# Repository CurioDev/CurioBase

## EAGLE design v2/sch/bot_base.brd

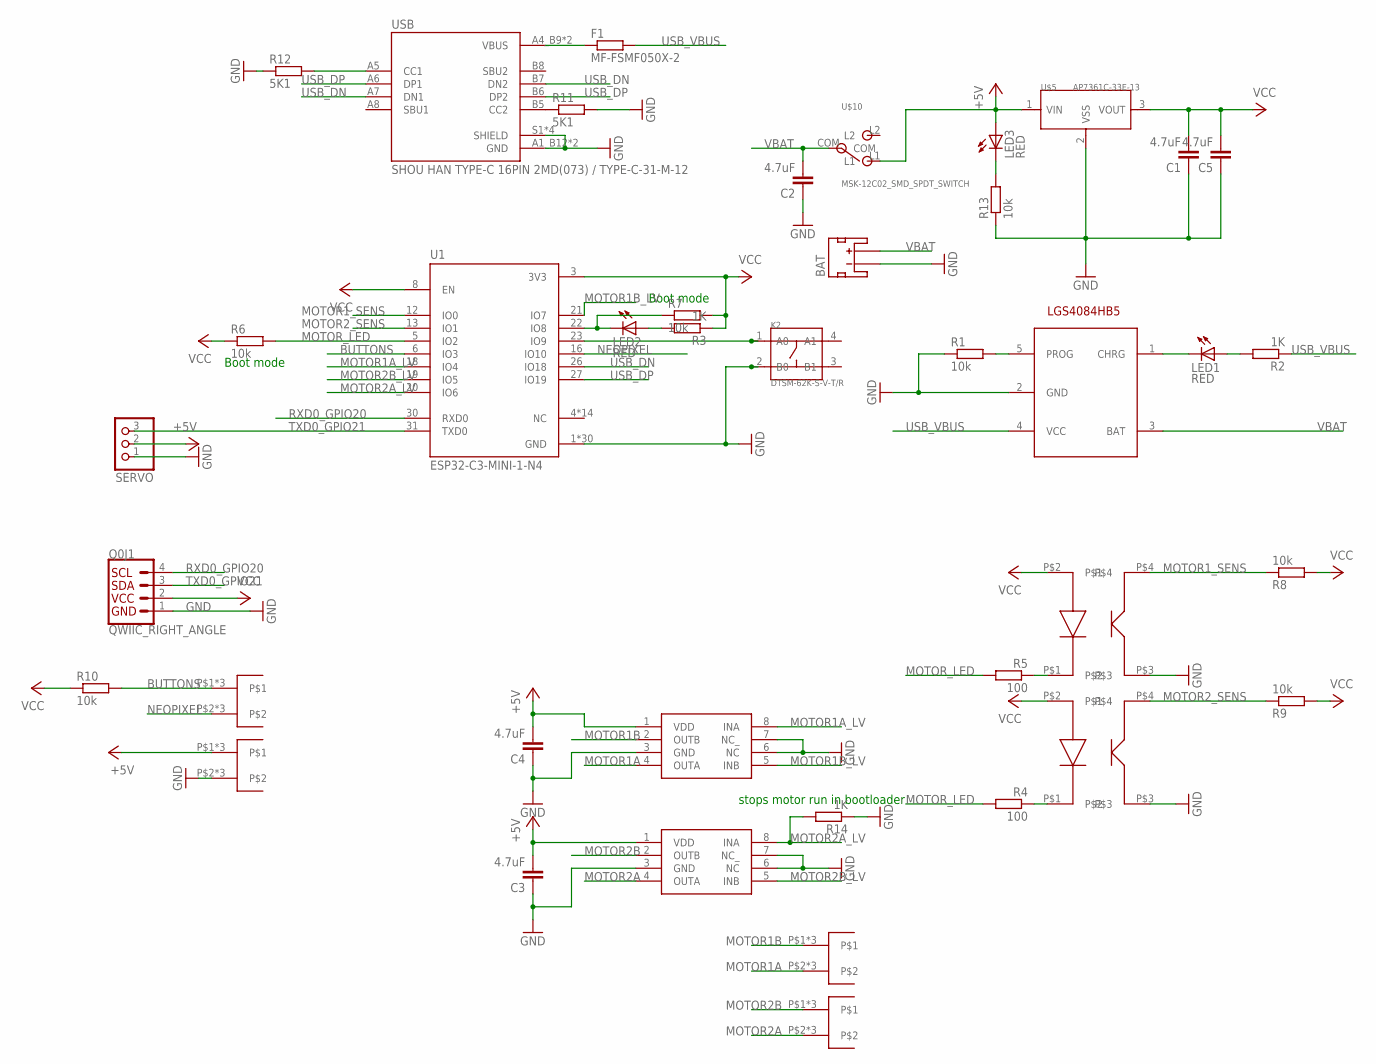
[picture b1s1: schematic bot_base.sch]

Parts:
BAT: C47647 / S2B-PH-SM4-TB; JST-2-SMD
C1, C2, C3, C4, C5: 4.7uF; C0805
F1: MF-FSMF050X-2; R0603
K2: DTSM-62K-S-V-T/R; SW4-SMD-6.0X6.0X5.0MM
LED1, LED2, LED3: RED; CHIPLED_0603
Q0: QWIIC_RIGHT_ANGLE; JST04_1MM_RA
R1, R6, R7, R8, R9, R10, R13: 10k; R0603
R2, R3, R14: 1K; R0603
R4, R5: 100; R0603
R11, R12: 5K1; R0603
SERVO: PINHD-1X03_2.54-S; 1X03-S
U1: ESP32-C3-MINI-1-N4; XCVR_ESP32-C3-MINI-1-N4
U4: LGS4084HB5; SOT23-5
U$1, U$2: XL-ITR9707
U$3, U$4: GR6205; SOP8
U$5: AP7361C-33E-13; SOT223
U$6, U$7, U$8, U$9: PCBSIDE2
U$10: MSK-12C02_SMD_SPDT_SWITCH; MSK-12C02
USB: SHOU HAN TYPE-C 16PIN 2MD(073) / TYPE-C-31-M-12; HRO_TYPE-C-31-M-12

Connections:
+5V: C3.2, C4.2, LED3.A, SERVO.2, U$3.1 (VDD), U$4.1 (VDD), U$5.1 (VIN), U$9.P$1, U$9.P$3, U$9.P$4, U$10.L1
BOOT: K2.1 (A0), U1.23 (IO9)
BUTTONS: R10.2, U1.6 (IO3), U$8.P$1, U$8.P$3, U$8.P$4
GND: BAT.1 (-), C1.1, C2.1, C3.1, C4.1, C5.1, K2.2 (B0), Q0.1, R1.1, R11.2, R12.1, R13.1, R14.1, SERVO.1, U1.1 (GND), U1.2 (GND), U1.11 (GND), U1.14 (GND), U1.36 (GND), U1.37 (GND), U1.38 (GND), U1.39 (GND), U1.40 (GND), U1.41 (GND), U1.42 (GND), U1.43 (GND), U1.44 (GND), U1.45 (GND), U1.46 (GND), U1.47 (GND), U1.48 (GND), U1.49_1 (GND), U1.49_2 (GND), U1.49_3 (GND), U1.49_4 (GND), U1.49_5 (GND), U1.49_6 (GND), U1.49_7 (GND), U1.49_8 (GND), U1.49_9 (GND), U1.50 (GND), U1.51 (GND), U1.52 (GND), U1.53 (GND), U4.2 (GND), U$1.P$3, U$2.P$3, U$3.3 (GND), U$3.6 (NC), U$3.7 (NC_), U$4.3 (GND), U$4.6 (NC), U$4.7 (NC_), U$5.2 (VSS), U$9.P$2, U$9.P$5, U$9.P$6, USB.A1_B12 (GND), USB.B1_A12 (GND), USB.S1 (SHIELD), USB.S2 (SHIELD), USB.S3 (SHIELD), USB.S4 (SHIELD)
MOTOR1A: U$3.4 (OUTA), U$6.P$2, U$6.P$5, U$6.P$6
MOTOR1A_LV: U1.18 (IO4), U$3.8 (INA)
MOTOR1B: U$3.2 (OUTB), U$6.P$1, U$6.P$3, U$6.P$4
MOTOR1B_LV: U1.21 (IO7), U$3.5 (INB)
MOTOR1_SENS: R8.1, U1.12 (IO0), U$1.P$4
MOTOR2A: U$4.4 (OUTA), U$7.P$2, U$7.P$5, U$7.P$6
MOTOR2A_LV: R14.2, U1.20 (IO6), U$4.8 (INA)
MOTOR2B: U$4.2 (OUTB), U$7.P$1, U$7.P$3, U$7.P$4
MOTOR2B_LV: U1.19 (IO5), U$4.5 (INB)
MOTOR2_SENS: R9.1, U1.13 (IO1), U$2.P$4
MOTOR_LED: R4.2, R5.2, R6.2, U1.5 (IO2)
unnamed: LED1.C, U4.1 (CHRG)
unnamed: LED3.C, R13.2
unnamed: R5.1, U$1.P$1
unnamed: LED1.A, R2.2
unnamed: R4.1, U$2.P$1
unnamed: LED2.A, R3.2
unnamed: R11.1, USB.B5 (CC2)
unnamed: LED2.C, R7.1, U1.22 (IO8)
unnamed: R12.2, USB.A5 (CC1)
unnamed: R1.2, U4.5 (PROG)
NEOPIXEL: U1.16 (IO10), U$8.P$2, U$8.P$5, U$8.P$6
RXD0_GPIO20: Q0.4, U1.30 (RXD0)
TXD0_GPIO21: Q0.3, SERVO.3, U1.31 (TXD0)
USB_DN: U1.26 (IO18), USB.A7 (DN1), USB.B7 (DN2)
USB_DP: U1.27 (IO19), USB.A6 (DP1), USB.B6 (DP2)
USB_VBUS: F1.2, R2.1, U4.4 (VCC)
VBAT: BAT.2 (+), C2.2, U4.3 (BAT), U$10.COM
VBUS1: F1.1, USB.A4_B9 (VBUS), USB.B4_A9 (VBUS)
VCC: C1.2, C5.2, Q0.2, R3.1, R6.1, R7.2, R8.2, R9.2, R10.1, U1.3 (3V3), U1.8 (EN), U$1.P$2, U$2.P$2, U$5.3 (VOUT)

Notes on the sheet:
LGS4084HB5
Boot mode
stops motor run in bootloader

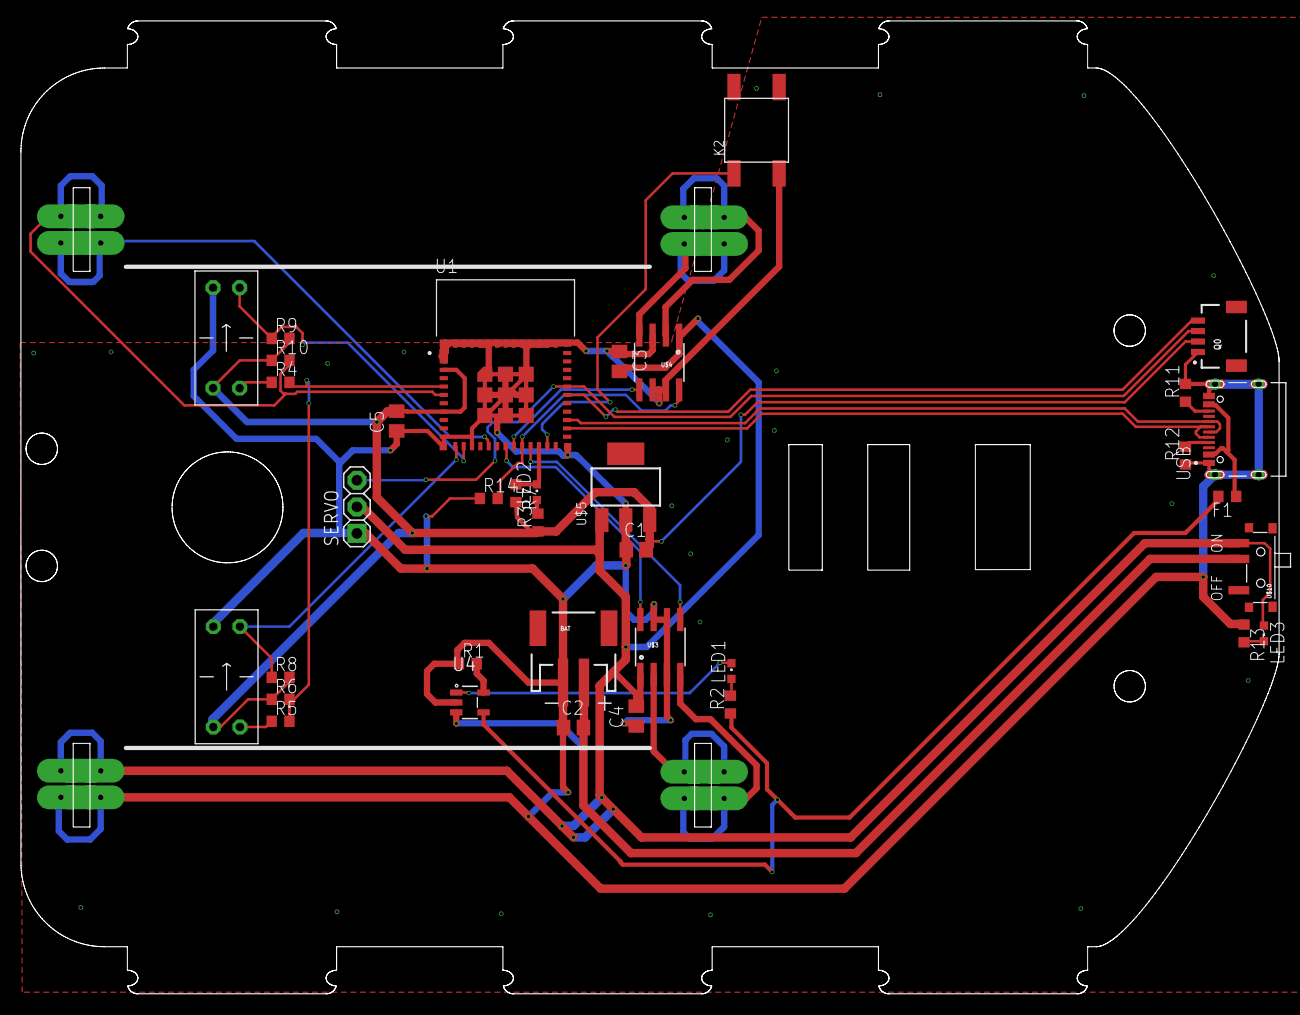
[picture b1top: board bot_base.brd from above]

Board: 2 copper layers, 120.3 x 93.0 mm, 40 parts (0 on the bottom side), 34 nets.

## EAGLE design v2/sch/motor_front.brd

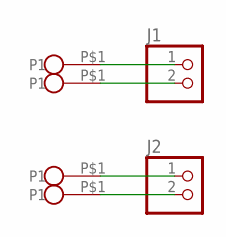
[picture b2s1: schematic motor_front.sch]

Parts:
J1, J2: PINHD-1X2; 1X02
U$1, U$2, U$3, U$4: BIGHOLE

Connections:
unnamed: J1.1, U$1.P$1
unnamed: J1.2, U$2.P$1
unnamed: J2.1, U$4.P$1
unnamed: J2.2, U$3.P$1

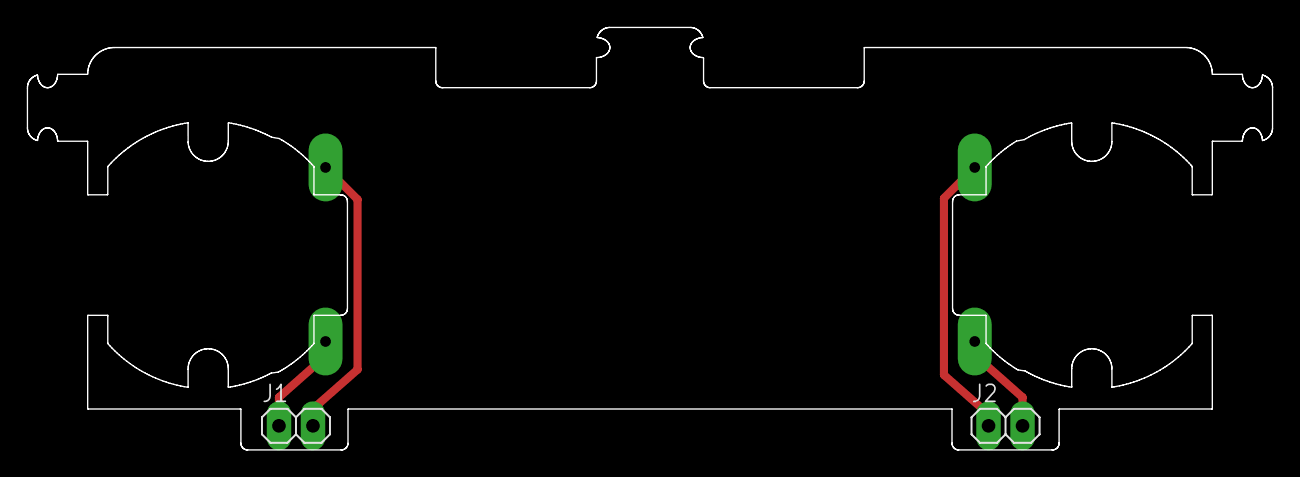
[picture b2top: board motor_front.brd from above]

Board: 2 copper layers, 93.0 x 31.6 mm, 6 parts (0 on the bottom side), 4 nets.

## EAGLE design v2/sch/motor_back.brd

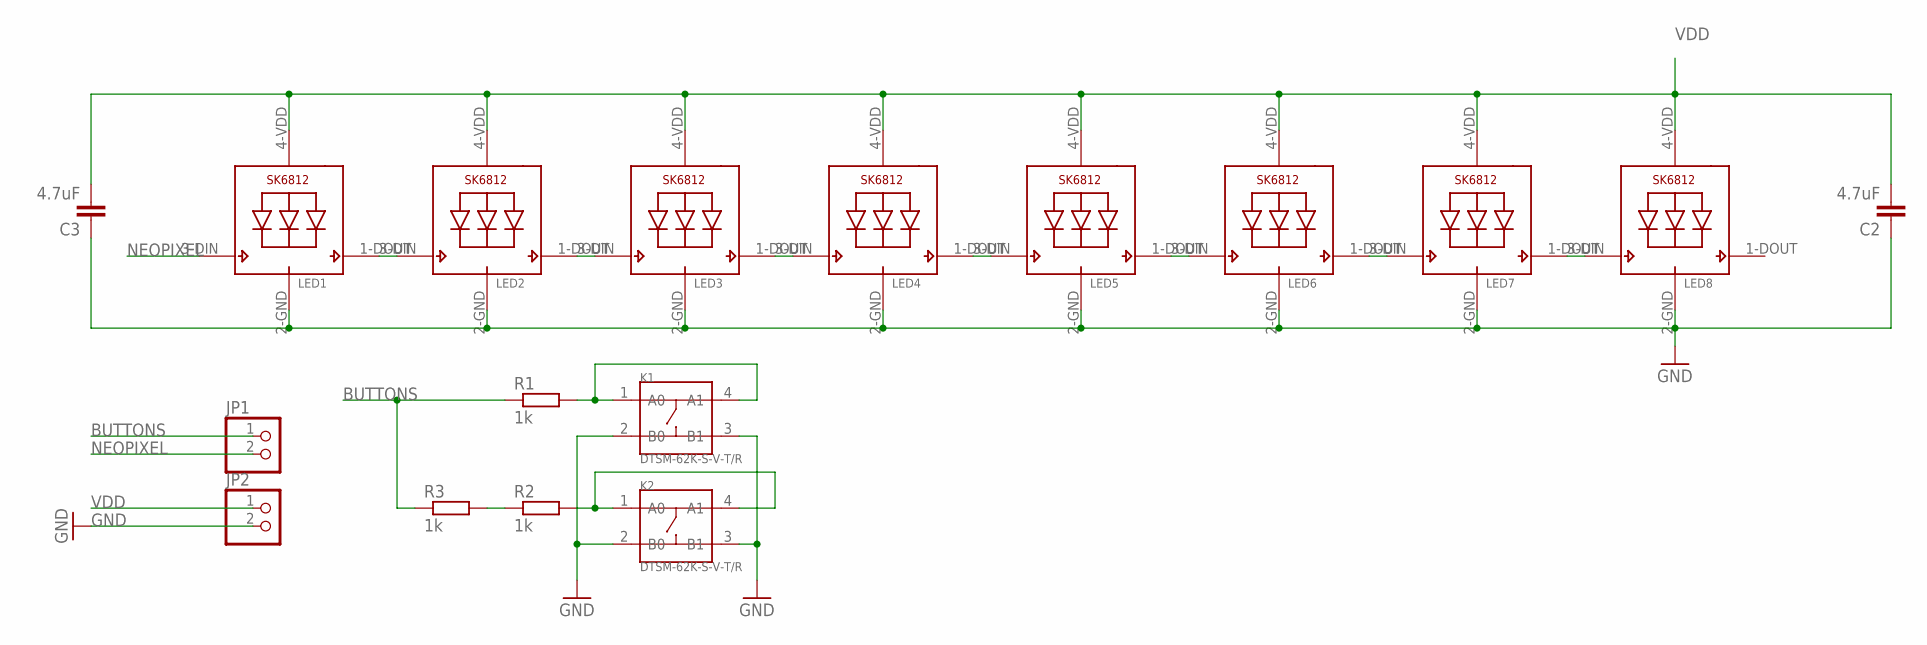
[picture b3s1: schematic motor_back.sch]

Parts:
C2, C3: 4.7uF; C0805
JP1, JP2: PINHD-1X2; 1X02
K1, K2: DTSM-62K-S-V-T/R; SW4-SMD-6.0X6.0X5.0MM
LED1, LED2, LED3, LED4, LED5, LED6, LED7, LED8: SK6812_3535; LED3535
R1, R2, R3: 1k; R0603

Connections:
BUTTONS: JP1.1, R1.1, R3.1
GND: C2.1, C3.1, JP2.2, K1.2 (B0), K1.3 (B1), K2.2 (B0), K2.3 (B1), LED1.2-GND (GND), LED2.2-GND (GND), LED3.2-GND (GND), LED4.2-GND (GND), LED5.2-GND (GND), LED6.2-GND (GND), LED7.2-GND (GND), LED8.2-GND (GND)
unnamed: LED1.1-DOUT (DO), LED2.3-DIN (DI)
unnamed: LED2.1-DOUT (DO), LED3.3-DIN (DI)
unnamed: LED3.1-DOUT (DO), LED4.3-DIN (DI)
unnamed: LED4.1-DOUT (DO), LED5.3-DIN (DI)
unnamed: LED5.1-DOUT (DO), LED6.3-DIN (DI)
unnamed: LED6.1-DOUT (DO), LED7.3-DIN (DI)
unnamed: LED7.1-DOUT (DO), LED8.3-DIN (DI)
unnamed: K1.1 (A0), K1.4 (A1), R1.2
unnamed: K2.1 (A0), K2.4 (A1), R2.2
unnamed: R2.1, R3.2
NEOPIXEL: JP1.2, LED1.3-DIN (DI)
VDD: C2.2, C3.2, JP2.1, LED1.4-VDD (VDD), LED2.4-VDD (VDD), LED3.4-VDD (VDD), LED4.4-VDD (VDD), LED5.4-VDD (VDD), LED6.4-VDD (VDD), LED7.4-VDD (VDD), LED8.4-VDD (VDD)

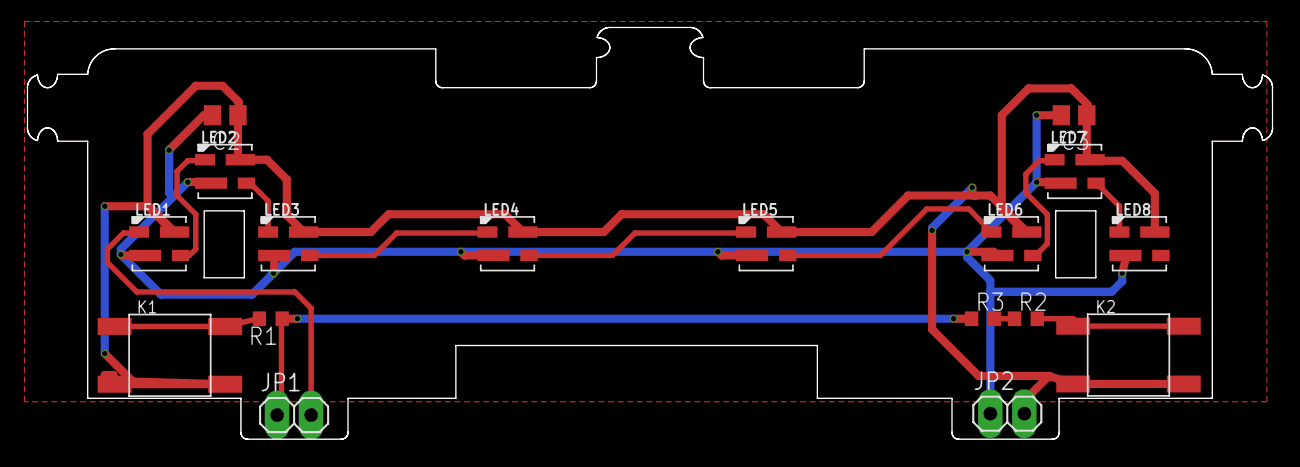
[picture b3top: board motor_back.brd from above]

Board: 2 copper layers, 93.0 x 30.8 mm, 17 parts (0 on the bottom side), 14 nets.

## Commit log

2022-11-30 Initial ideas
2022-11-30 oops
2023-01-11 building bot up - it's easier to have separate DXF for each part
2023-01-12 split up bot parts
2023-01-12 tweaked design, allowing almost flat
2023-01-12 widened robot to allow elastic over wider phones
2023-02-08 slightly more complete design
2023-02-08 mk 1
2023-02-09 STLs
2023-03-30 adding battery and PCB
2023-03-31 recent updates
2023-03-31 remove phone clips, put indents for rubber bands
2023-04-03 shrink phone holder elastic band clip
2023-04-19 generated files
2023-04-19 adding angle markings on sides
2023-04-19 widen slots for phone alignment and round edges
2023-05-03 update phone base svg
2023-05-22 most recent tweaks
2023-06-23 Updated with new side panels and updated phone holder
2024-03-22 move v1
2024-03-22 first v2 attempt
2024-03-22 add something to stop the phone slipping
2024-03-27 assembled in real life and mostly ok
2024-04-24 Updated design with 10/25/40 phone angles and elastic bang grips
2024-05-17 initial schematics
2024-05-21 routing almost finished
2024-05-24 first protos sent off
2024-05-24 switch update
2024-06-12 mid-update, fixing issues
2024-06-21 latest relayout
2024-07-22 add bumpers
2024-07-25 update for most recent prototypes
2024-10-18 adding test JS code
2024-10-18 updated fw

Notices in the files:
parts and their libraries:
SparkFun-Connectors: Licensing: Creative Commons ShareAlike 4.0 International - https://creativecommons.org/licenses/by-sa/4.0
